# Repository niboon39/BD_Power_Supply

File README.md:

# BD_Power_Supply
Bead_Board_Power_Supply 5V

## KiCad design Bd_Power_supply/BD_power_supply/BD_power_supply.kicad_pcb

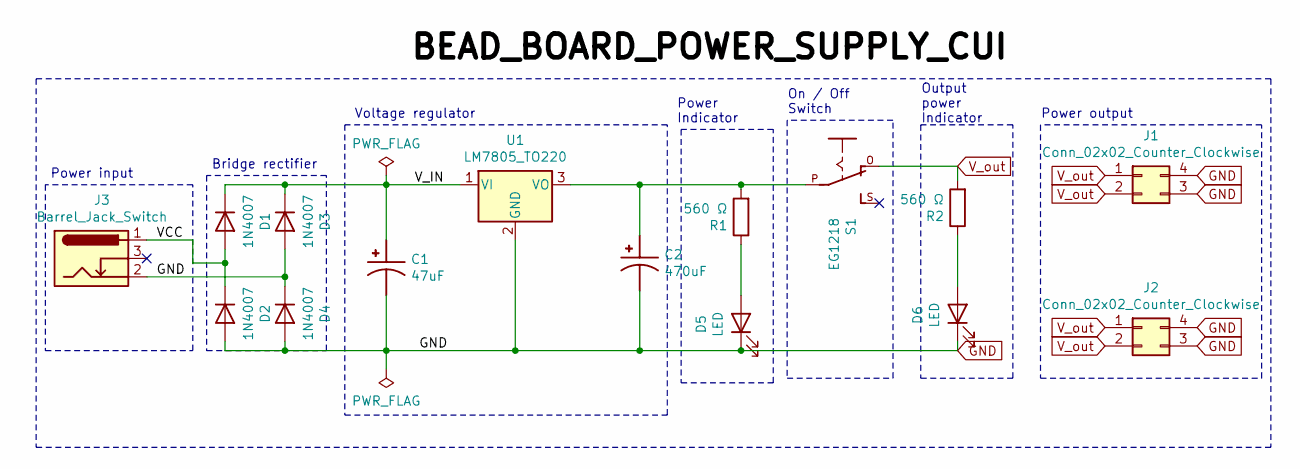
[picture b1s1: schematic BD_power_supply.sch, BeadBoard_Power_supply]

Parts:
C1: 47uF; CP_Radial_D4.0mm_P2.00mm; PARTREV 20-Dec-19
C2: 470uF; CP_Radial_D10.0mm_P5.00mm; PARTREV 20-Dec-19
D1, D2, D3, D4: 1N4007; D_DO-41_SOD81_P10.16mm_Horizontal
D5, D6: LED; LED_D3.0mm
J1, J2: Conn_02x02_Counter_Clockwise; PinSocket_2x02_P2.00mm_Vertical
J3: Barrel_Jack_Switch; BarrelJack_CUI_PJ-102AH_Horizontal
R1, R2: 560 Ω; R_Axial_DIN0204_L3.6mm_D1.6mm_P5.08mm_Horizontal
S1: EG1218
U1: LM7805_TO220; TO-220-3_Vertical

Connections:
/VCC: D1.2 (A), D2.1 (K), J3.1
/V_IN: C1.1, D1.1 (K), D3.1 (K), U1.1 (VI)
GND: C1.2, C2.2, D2.2 (A), D3.2 (A), D4.1 (K), D4.2 (A), D5.1 (K), D6.1 (K), J1.3, J1.4, J2.3, J2.4, J3.2, U1.2 (GND)
unnamed: C2.1, R1.2, S1.P, U1.3 (VO)
unnamed: D5.2 (A), R1.1
unnamed: D6.2 (A), R2.1
V_out: J1.1, J1.2, J2.1, J2.2, R2.2, S1.O

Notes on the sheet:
Power input
Bridge rectifier
Voltage regulator
Power Indicator
On / Off Switch
Output power Indicator
Power output

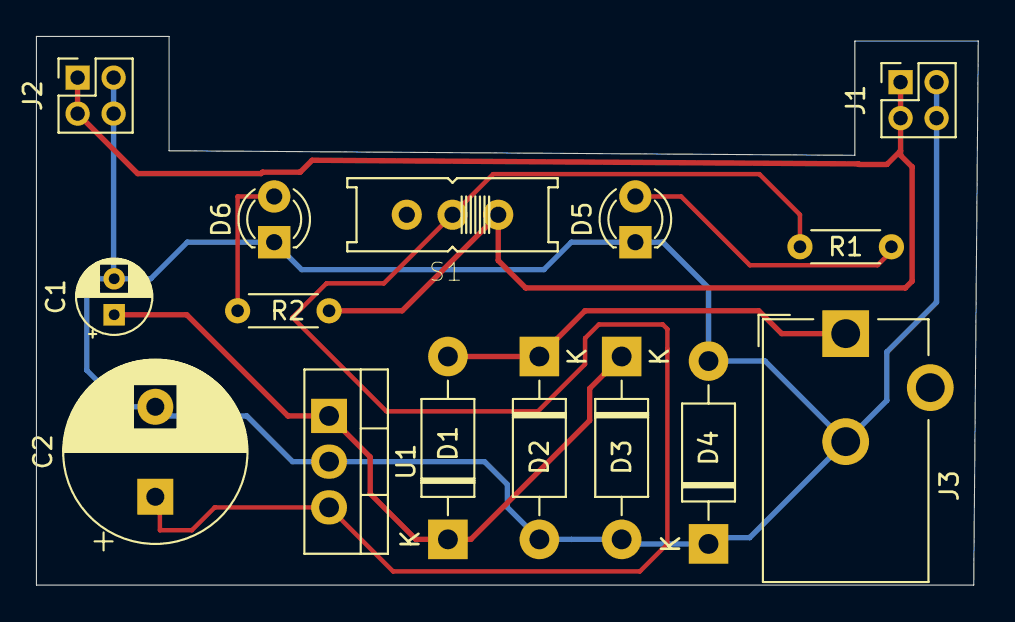
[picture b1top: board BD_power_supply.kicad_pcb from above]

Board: 2 copper layers, 52.3 x 30.5 mm, 15 parts (0 on the bottom side), 7 nets.
